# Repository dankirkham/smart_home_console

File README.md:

# Smart Home Console
ESP8266 IoT smart home console

## BOM
- NodeMCU V2

## nodemcu
Deploy to NodeMCU using ESPlorer.

## Heroku Deploy
Deploy nodemcu-relay submodule with `git subtree push --prefix nodemcu-relay heroku master` from `smart_home_console` directory.

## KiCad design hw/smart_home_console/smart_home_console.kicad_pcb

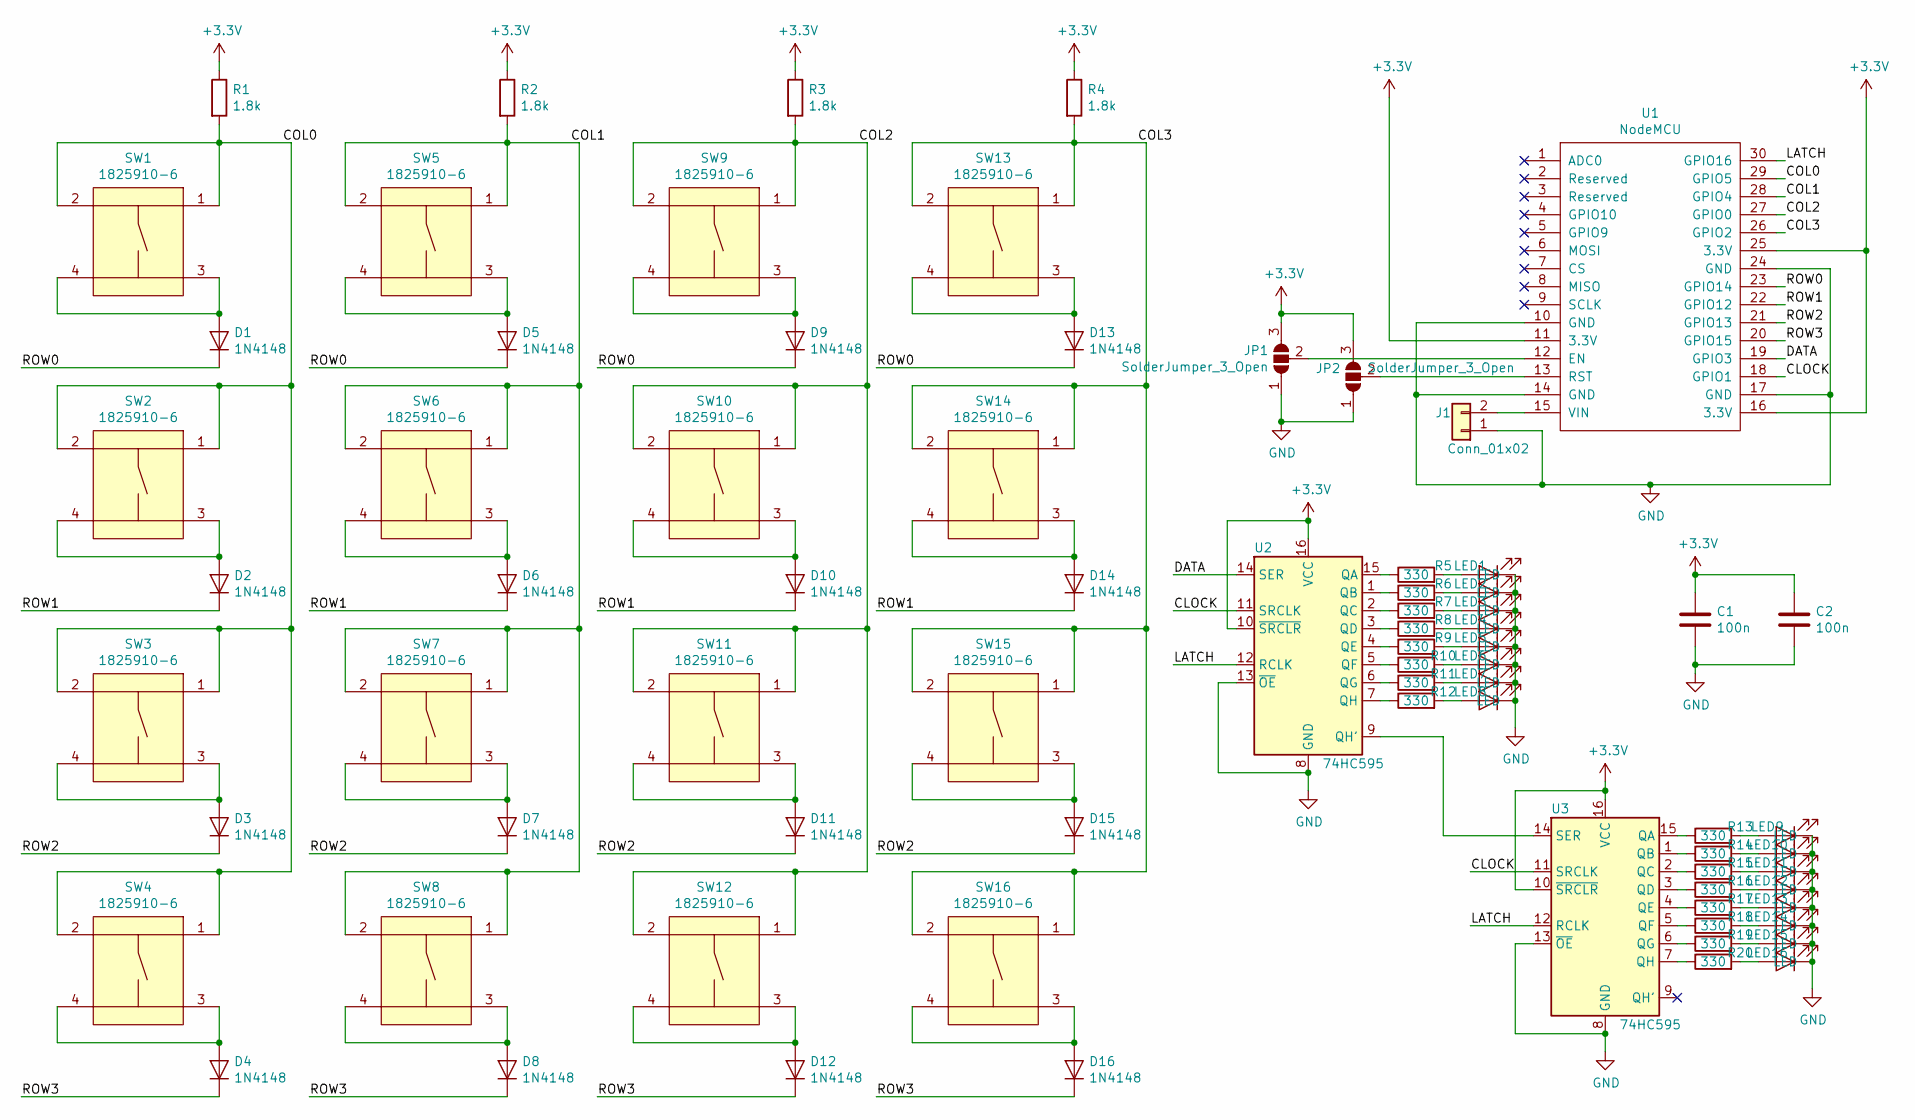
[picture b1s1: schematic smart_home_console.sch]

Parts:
C1, C2: 100n; C_Disc_D5.0mm_W2.5mm_P2.50mm
D1, D2, D3, D4, D5, D6, D7, D8, D9, D10, D11, D12, D13, D14, D15, D16: 1N4148; D_DO-35_SOD27_P7.62mm_Horizontal
J1: Conn_01x02; WireConnection_2.00mmDrill
JP1, JP2: SolderJumper_3_Open; SolderJumper-3_P1.3mm_Open_RoundedPad1.0x1.5mm_NumberLabels
LED1, LED2, LED3, LED4, LED5, LED6, LED7, LED8, LED9, LED10, LED11, LED12, LED13, LED14, LED15, LED16: LED; LED_D3.0mm
R1, R2, R3, R4: 1.8k; R_0805_HandSoldering
R5, R6, R7, R8, R9, R10, R11, R12, R13, R14, R15, R16, R17, R18, R19, R20: 330; R_0805_HandSoldering
SW1, SW2, SW3, SW4, SW5, SW6, SW7, SW8, SW9, SW10, SW11, SW12, SW13, SW14, SW15, SW16: 1825910-6
U1: NodeMCU; NodeMCUV2
U2, U3: 74HC595; DIP-16_W7.62mm

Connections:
+3V3: C1.1, C2.1, JP1.3 (B), JP2.3 (B), R1.1, R2.1, R3.1, R4.1, U1.11 (3.3V), U1.16 (3.3V), U1.25 (3.3V), U2.10 (~SRCLR), U2.16 (VCC), U3.10 (~SRCLR), U3.16 (VCC)
/CLOCK: U1.18 (GPIO1), U2.11 (SRCLK), U3.11 (SRCLK)
/COL0: R1.2, SW1.1, SW1.2, SW2.1, SW2.2, SW3.1, SW3.2, SW4.1, SW4.2, U1.29 (GPIO5)
/COL1: R2.2, SW5.1, SW5.2, SW6.1, SW6.2, SW7.1, SW7.2, SW8.1, SW8.2, U1.28 (GPIO4)
/COL2: R3.2, SW9.1, SW9.2, SW10.1, SW10.2, SW11.1, SW11.2, SW12.1, SW12.2, U1.27 (GPIO0)
/COL3: R4.2, SW13.1, SW13.2, SW14.1, SW14.2, SW15.1, SW15.2, SW16.1, SW16.2, U1.26 (GPIO2)
/DATA: U1.19 (GPIO3), U2.14 (SER)
/LATCH: U1.30 (GPIO16), U2.12 (RCLK), U3.12 (RCLK)
/ROW0: D1.1 (K), D5.1 (K), D9.1 (K), D13.1 (K), U1.23 (GPIO14)
/ROW1: D2.1 (K), D6.1 (K), D10.1 (K), D14.1 (K), U1.22 (GPIO12)
/ROW2: D3.1 (K), D7.1 (K), D11.1 (K), D15.1 (K), U1.21 (GPIO13)
/ROW3: D4.1 (K), D8.1 (K), D12.1 (K), D16.1 (K), U1.20 (GPIO15)
GND: C1.2, C2.2, J1.1, JP1.1 (A), JP2.1 (A), LED1.1 (K), LED2.1 (K), LED3.1 (K), LED4.1 (K), LED5.1 (K), LED6.1 (K), LED7.1 (K), LED8.1 (K), LED9.1 (K), LED10.1 (K), LED11.1 (K), LED12.1 (K), LED13.1 (K), LED14.1 (K), LED15.1 (K), LED16.1 (K), U1.10 (GND), U1.14 (GND), U1.17 (GND), U1.24 (GND), U2.8 (GND), U2.13 (~OE), U3.8 (GND), U3.13 (~OE)
unnamed: D1.2 (A), SW1.3, SW1.4
unnamed: D2.2 (A), SW2.3, SW2.4
unnamed: D3.2 (A), SW3.3, SW3.4
unnamed: D4.2 (A), SW4.3, SW4.4
unnamed: D5.2 (A), SW5.3, SW5.4
unnamed: D6.2 (A), SW6.3, SW6.4
unnamed: D7.2 (A), SW7.3, SW7.4
unnamed: D8.2 (A), SW8.3, SW8.4
unnamed: D9.2 (A), SW9.3, SW9.4
unnamed: D10.2 (A), SW10.3, SW10.4
unnamed: D11.2 (A), SW11.3, SW11.4
unnamed: D12.2 (A), SW12.3, SW12.4
unnamed: D13.2 (A), SW13.3, SW13.4
unnamed: D14.2 (A), SW14.3, SW14.4
unnamed: D15.2 (A), SW15.3, SW15.4
unnamed: D16.2 (A), SW16.3, SW16.4
unnamed: J1.2, U1.15 (VIN)
unnamed: JP1.2 (C), U1.12 (EN)
unnamed: JP2.2 (C), U1.13 (RST)
unnamed: LED1.2 (A), R5.2
unnamed: LED2.2 (A), R6.2
unnamed: LED3.2 (A), R7.2
unnamed: LED4.2 (A), R8.2
unnamed: LED5.2 (A), R9.2
unnamed: LED6.2 (A), R10.2
unnamed: LED7.2 (A), R11.2
unnamed: LED8.2 (A), R12.2
unnamed: LED9.2 (A), R13.2
unnamed: LED10.2 (A), R14.2
unnamed: LED11.2 (A), R15.2
unnamed: LED12.2 (A), R16.2
unnamed: LED13.2 (A), R17.2
unnamed: LED14.2 (A), R18.2
unnamed: LED15.2 (A), R19.2
unnamed: LED16.2 (A), R20.2
unnamed: R5.1, U2.15 (QA)
unnamed: R6.1, U2.1 (QB)
unnamed: R7.1, U2.2 (QC)
unnamed: R8.1, U2.3 (QD)
unnamed: R9.1, U2.4 (QE)
unnamed: R10.1, U2.5 (QF)
unnamed: R11.1, U2.6 (QG)
unnamed: R12.1, U2.7 (QH)
unnamed: R13.1, U3.15 (QA)
unnamed: R14.1, U3.1 (QB)
unnamed: R15.1, U3.2 (QC)
unnamed: R16.1, U3.3 (QD)
unnamed: R17.1, U3.4 (QE)
unnamed: R18.1, U3.5 (QF)
unnamed: R19.1, U3.6 (QG)
unnamed: R20.1, U3.7 (QH)
unnamed: U2.9 (QH'), U3.14 (SER)

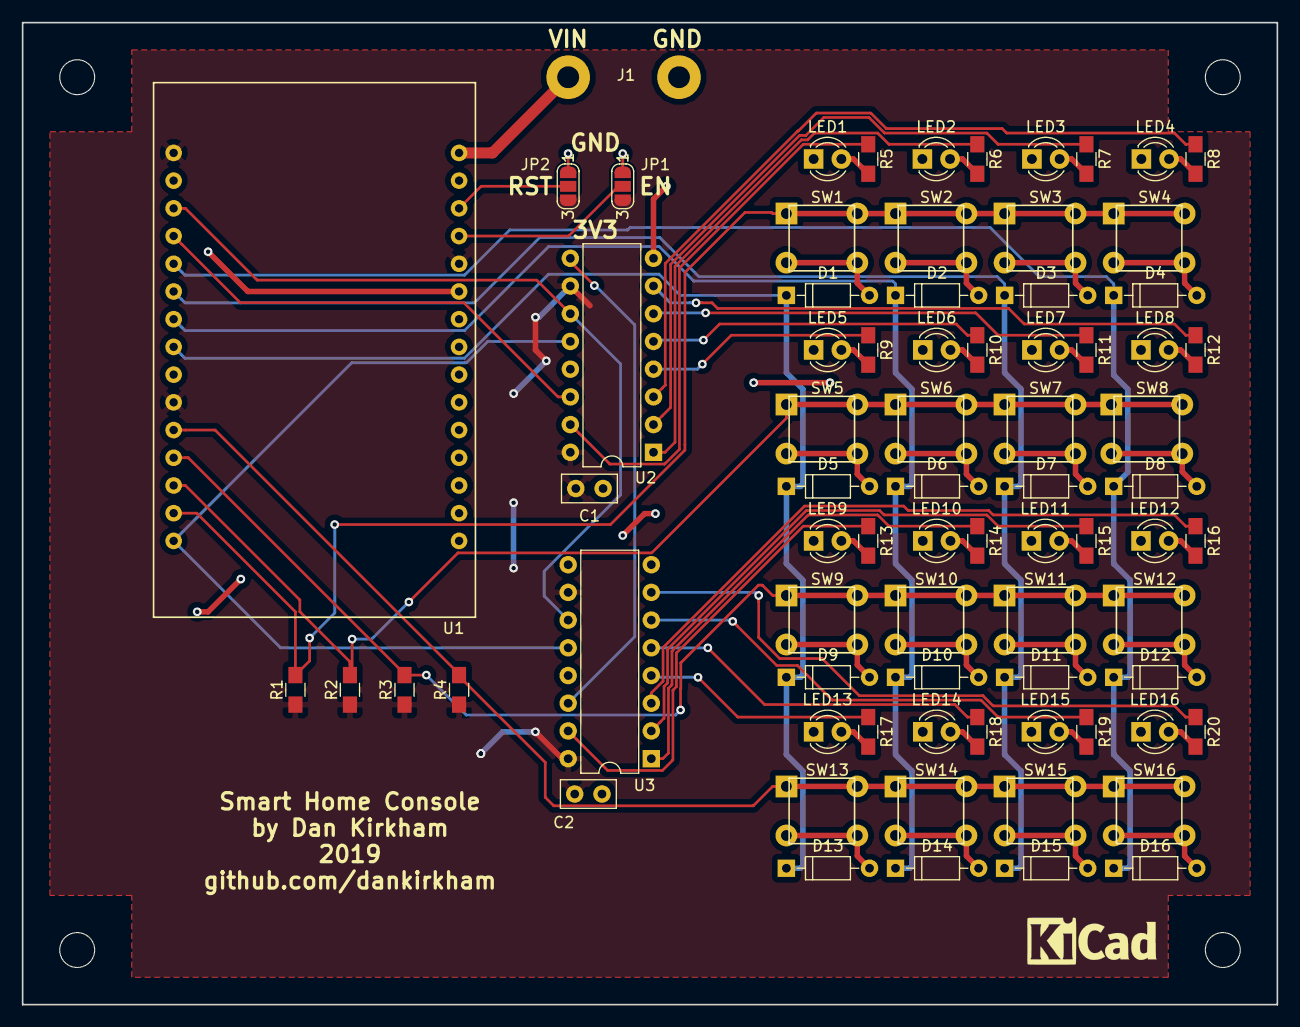
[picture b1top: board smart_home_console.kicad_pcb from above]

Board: 2 copper layers, 115.0 x 90.0 mm, 76 parts (0 on the bottom side), 65 nets.

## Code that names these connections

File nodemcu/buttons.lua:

local gpio = require("gpio")

local lib = {}

PIN_COL0 = 1 -- GPIO5
PIN_COL1 = 2 -- GPIO4
PIN_COL2 = 3 -- GPIO0
PIN_COL3 = 4 -- GPIO2
PIN_ROW0 = 5 -- GPIO14
PIN_ROW1 = 6 -- GPIO12
PIN_ROW2 = 7 -- GPIO13
PIN_ROW3 = 8 -- GPIO15

local debounce_timers = {0, 0, 0, 0, 0, 0, 0, 0, 0, 0, 0, 0, 0, 0, 0, 0}
local pressed = {0, 0, 0, 0, 0, 0, 0, 0, 0, 0, 0, 0, 0, 0, 0, 0}

function select_row(row)
    gpio.write(PIN_ROW0, gpio.HIGH)
    gpio.write(PIN_ROW1, gpio.HIGH)
    gpio.write(PIN_ROW2, gpio.HIGH)
    gpio.write(PIN_ROW3, gpio.HIGH)

    if row == 0 then
        gpio.write(PIN_ROW0, gpio.LOW)
    elseif row == 1 then
        gpio.write(PIN_ROW1, gpio.LOW)
    elseif row == 2 then
        gpio.write(PIN_ROW2, gpio.LOW)
    else
        gpio.write(PIN_ROW3, gpio.LOW)
    end
end

function lib.init_buttons()
    gpio.mode(PIN_COL0, gpio.INPUT)
    gpio.mode(PIN_COL1, gpio.INPUT)
    gpio.mode(PIN_COL2, gpio.INPUT)
    gpio.mode(PIN_COL3, gpio.INPUT)

    gpio.mode(PIN_ROW0, gpio.OPENDRAIN)
    gpio.mode(PIN_ROW1, gpio.OPENDRAIN)
    gpio.mode(PIN_ROW2, gpio.OPENDRAIN)
    gpio.mode(PIN_ROW3, gpio.OPENDRAIN)
end

function lib.read_buttons()
    -- Read Buttons
    local buttons = {false, false, false, false, false, false, false, false, false, false, false, false, false, false, false, false}
    for row = 0, 3 do
        select_row(row)
        buttons[4 * row + 1] = not (gpio.read(PIN_COL0) == 1)
        buttons[4 * row + 2] = not (gpio.read(PIN_COL1) == 1)
        buttons[4 * row + 3] = not (gpio.read(PIN_COL2) == 1)
        buttons[4 * row + 4] = not (gpio.read(PIN_COL3) == 1)
    end

    -- Remap the buttons (transpose)
    buttons = {
        buttons[1],
        buttons[5],
        buttons[9],
        buttons[13],

        buttons[2],
        buttons[6],
        buttons[10],
        buttons[14],

        buttons[3],
        buttons[7],
        buttons[11],
        buttons[15],

        buttons[4],
        buttons[8],
        buttons[12],
        buttons[16]
    }

    -- Check for debounce
    local posedge_buttons = {}
    for i = 1, 16 do
        posedge_buttons[i] = false

        -- Check for positive edge
        if (
          (not pressed[i]) and -- Not in press state
          buttons[i] and -- Physically pressed
          debounce_timers[i] == 0 -- Not debouncing
        ) then
            pressed[i] = true;
            posedge_buttons[i] = true -- Save posedge
            debounce_timers[i] = 3
        end

        -- Check for negative edge
        if (
          pressed[i] and -- In press state
          (not buttons[i]) and -- Not physically pressed
          debounce_timers[i] == 0 -- Not debouncing
        ) then
            pressed[i] = false;
            debounce_timers[i] = 3
        end

        -- Tick debounce timers
        if debounce_timers[i] > 0 then
            debounce_timers[i] = debounce_timers[i] - 1
        end
    end

    -- Return posedge
    return posedge_buttons
end

return lib

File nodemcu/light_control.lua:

local gpio = require("gpio")

local lib = {}

PIN_DATA = 9 -- GPIO3
PIN_CLOCK = 10 -- GPIO1
PIN_LATCH = 0 -- GPIO0

function lib.set_lights(lights)
    gpio.write(PIN_DATA, gpio.LOW)
    gpio.write(PIN_CLOCK, gpio.LOW)
    gpio.write(PIN_LATCH, gpio.LOW)

    for i = 16, 1, -1 do
        if lights[i] == true then
            gpio.write(PIN_DATA, gpio.HIGH)
        else
            gpio.write(PIN_DATA, gpio.LOW)
        end

        gpio.write(PIN_CLOCK, gpio.HIGH)
        gpio.write(PIN_CLOCK, gpio.LOW)
    end

    gpio.write(PIN_LATCH, gpio.HIGH)
    gpio.write(PIN_LATCH, gpio.LOW)
end

function lib.init_lights(lights)
    gpio.mode(PIN_DATA, gpio.OUTPUT)
    gpio.mode(PIN_CLOCK, gpio.OUTPUT)
    gpio.mode(PIN_LATCH, gpio.OUTPUT)

    lib.set_lights({false, false, false, false, false, false, false, false, false, false, false, false, false, false, false, false})
end

return lib

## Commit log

2019-11-26 Initial Commit.
2019-11-26 Add NodeMCU project.
2019-11-26 Change to PUT request.
2019-11-27 Get NodeMCU working.
2019-12-05 Web app.
2019-12-05 Web App working.
2019-12-05 Deploy site.
2020-03-14 Bump acorn from 7.1.0 to 7.1.1 in /nodemcu-relay
    Bumps [acorn](https://github.com/acornjs/acorn) from 7.1.0 to 7.1.1.
    - [Release notes](https://github.com/acornjs/acorn/releases)
    - [Commits](https://github.com/acornjs/acorn/compare/7.1.0...7.1.1)
2020-09-05 Use MQTT to integrate with Home Assistant.
2020-09-05 Bump acorn from 7.1.0 to 7.4.0 in /nodemcu-relay
    Bumps [acorn](https://github.com/acornjs/acorn) from 7.1.0 to 7.4.0.
    - [Release notes](https://github.com/acornjs/acorn/releases)
    - [Commits](https://github.com/acornjs/acorn/compare/7.1.0...7.4.0)
2020-09-05 Refactor and commit a bare config file
2020-09-05 Make readme.
2020-09-05 Update readme.
2020-09-05 Skookumfacted debounce logic.
2021-06-10 Bump normalize-url from 4.5.0 to 4.5.1 in /nodemcu-relay
    Bumps [normalize-url](https://github.com/sindresorhus/normalize-url) from 4.5.0 to 4.5.1.
    - [Release notes](https://github.com/sindresorhus/normalize-url/releases)
    - [Commits](https://github.com/sindresorhus/normalize-url/commits)
    ---
    updated-dependencies:
    - dependency-name: normalize-url
2021-06-10 Bump glob-parent from 5.1.0 to 5.1.2 in /nodemcu-relay
    Bumps [glob-parent](https://github.com/gulpjs/glob-parent) from 5.1.0 to 5.1.2.
    - [Release notes](https://github.com/gulpjs/glob-parent/releases)
    - [Changelog](https://github.com/gulpjs/glob-parent/blob/main/CHANGELOG.md)
    - [Commits](https://github.com/gulpjs/glob-parent/compare/v5.1.0...v5.1.2)
    ---
    updated-dependencies:
